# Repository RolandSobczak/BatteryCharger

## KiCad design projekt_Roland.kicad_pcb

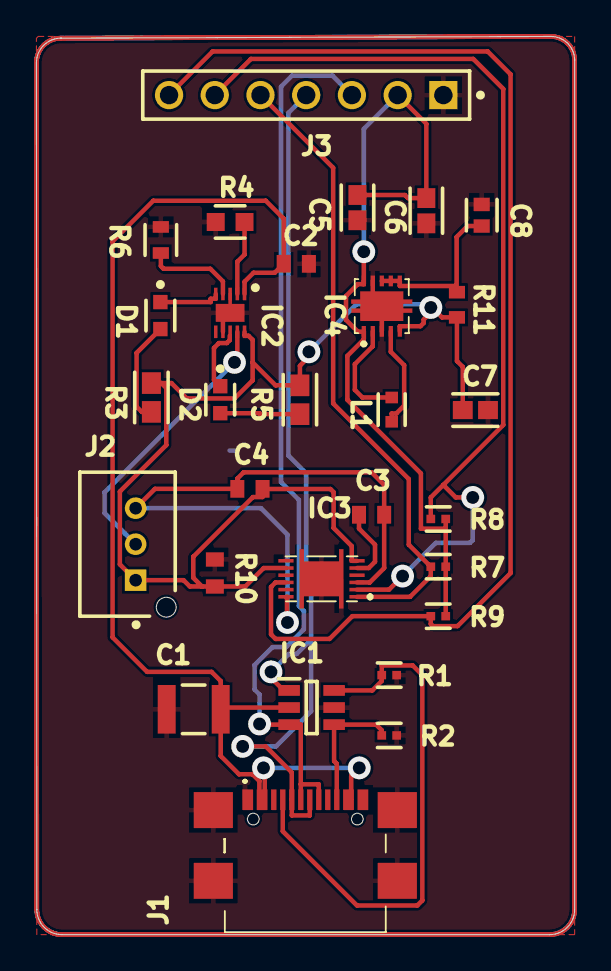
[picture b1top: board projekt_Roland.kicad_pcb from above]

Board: 2 copper layers, 29.9 x 49.9 mm, 29 parts (0 on the bottom side), 23 nets.

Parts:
C1: 0.1uF; FP-AC1210-0_85-MFG
C2, C4: 1uF; CAPC1608X90N
C3: 0.47uF; CAPC1608X90N
C5, C6, C7: 10uF; FP-GRM188-0_2-IPC_B
C8: 0.1uF; FP-C0603C-CF-MFG
D1, D2: LG Q396-PS-35; FP-LG_Q396-MFG
IC1: TPD4E001RDBVR; SOT95P280X145-6N
IC2: BQ24040DSQR; SON40P200X200X80-11N
IC3: BQ27441DRZR-G1A; BQ27441DRZRG1A
IC4: TPS63001DRCR; TPS74901DRCR
J1: USB4110-GF-A; USB4110GFA
J2: B03B-PASK-1(LF)(SN); FP-B03B-PASK-1_LF_SN-MFG
J3: TSW-107-07-G-S; FP-TSW-107-07-G-S-MFG
L1: 2.2uH; FP-LQM18PN_D0-MFG
R1, R2, R7, R8, R9: 5.1k; FP-RN73R1E-IPC_C
R3, R5: 1.5kΩ; FP-RMCF0603-IPC_A
R4: 1kΩ; FP-TFCR0603-MFG
R6: 2kΩ; FP-RMCF0603-MFG
R10: 0.01ohm; RESC1608X40X30ML10T10
R11: 100; RESC1608X55X25NL10T15

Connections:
GND: C1.2, C2.2, C5.2, C6.2, C7.2, C8.2, IC1.5, IC2.3, IC2.7, IC2.11, IC3.7, IC3.13, IC3.14, IC3.15, IC4.3, IC4.9, IC4.11, IC4.12, IC4.13, IC4.14, IC4.15, J1.A1, J1.A12, J1.B1, J1.B12, J1.MP1, J1.MP2, J1.MP3, J1.MP4, J3.1, R1.2, R2.2, R4.2, R6.2, R10.2
NetC3_1: C3.1, IC3.5
NetC3_2: C3.2, C4.2, IC3.3, IC3.12, J2.3
NetC4_1: C4.1, C7.1, IC2.10, IC3.6, IC3.8, IC4.5, J2.1, R3.2, R5.2, R10.1, R11.1
NetC8_1: C8.1, IC4.6, IC4.7, IC4.8, R11.2
NetD1_1: D1.1, IC2.5
NetD1_2: D1.2, R3.1
NetD2_1: D2.1, IC2.8
NetD2_2: D2.2, R5.1
NetIC1_1: IC1.1, J1.A7, J1.B7, J3.4
NetIC1_3: IC1.3, J1.A6, J1.B6, J3.3
NetIC1_4: IC1.4, J1.B5, R2.1
NetIC1_6: IC1.6, J1.A5, R1.1
NetIC2_2: IC2.2, R4.1
NetIC2_4: IC2.4, R6.1
NetIC2_9: IC2.9, J2.2
NetIC3_1: IC3.1, J3.5, R7.2
NetIC3_2: IC3.2, J3.6, R8.2
NetIC3_10: IC3.10, J3.7, R9.2
NetIC4_2: IC4.2, L1.2
NetIC4_4: IC4.4, L1.1
VBUS: C1.1, C2.1, IC1.2, IC2.1, J1.A4, J1.A9, J1.B4, J1.B9
VCC: C5.1, C6.1, IC4.1, IC4.10, J3.2, R7.1, R8.1, R9.1

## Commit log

2026-04-20 feat: kicad symbols/footprings/3Dmodels
2026-04-21 feat: schematic v1
2026-04-21 fix: Buck Converter inductor changed to the right type
